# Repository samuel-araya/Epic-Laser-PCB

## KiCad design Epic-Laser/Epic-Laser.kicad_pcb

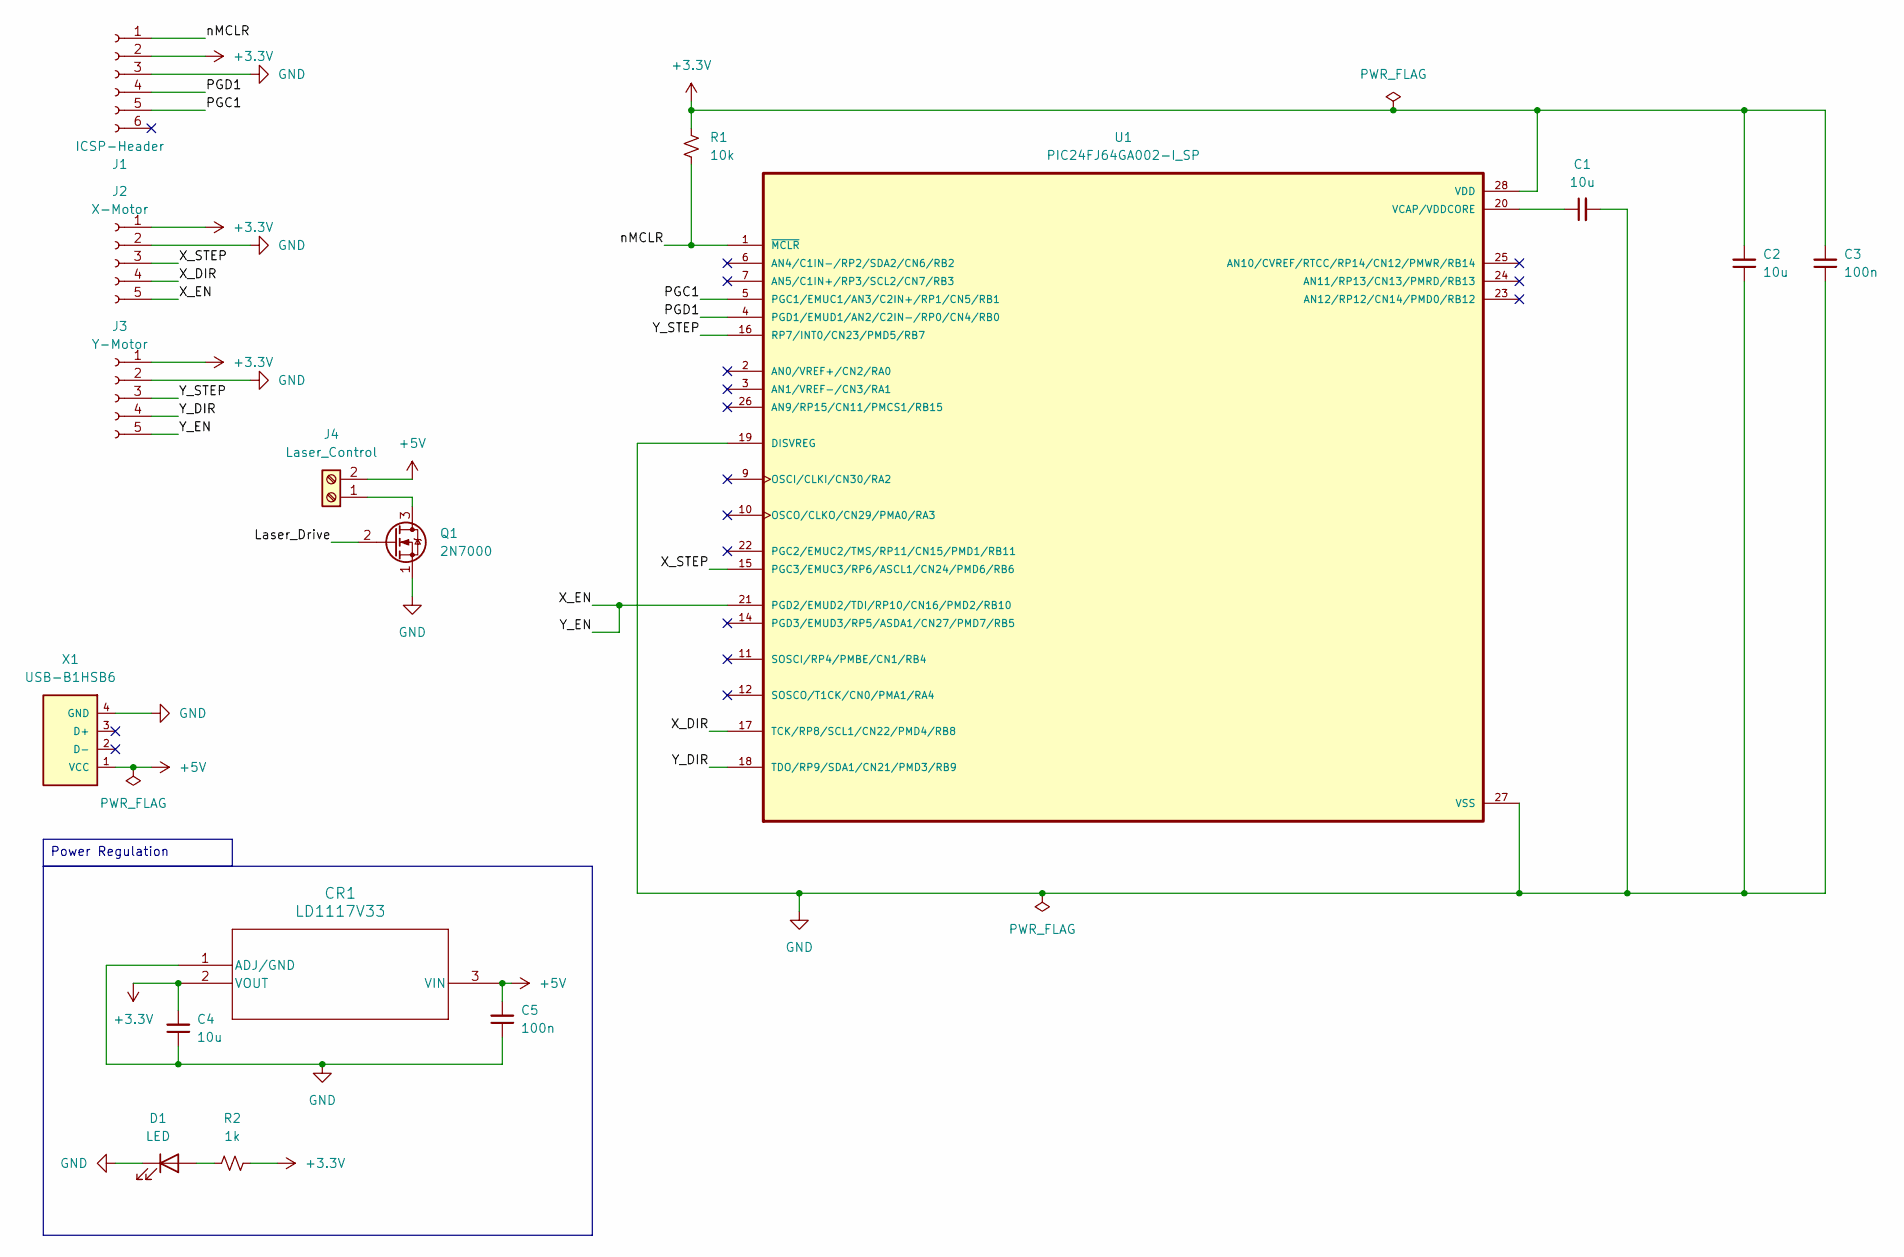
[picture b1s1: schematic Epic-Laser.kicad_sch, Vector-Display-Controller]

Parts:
C1, C2, C4: 10u; C_Disc_D5.0mm_W2.5mm_P2.50mm
C3, C5: 100n; C_Disc_D5.0mm_W2.5mm_P2.50mm
CR1: LD1117V33; TO-220_STM
D1: LED
J1: ICSP-Header; PinSocket_1x07_P2.54mm_Vertical
J2: X-Motor
J3: Y-Motor
J4: Laser_Control
Q1: 2N7000; TO-92_Inline
R1: 10k; R_Axial_DIN0204_L3.6mm_D1.6mm_P5.08mm_Horizontal
R2: 1k
U1: PIC24FJ64GA002-I_SP; DIP787W46P254L3467H508Q28
X1: USB-B1HSB6; OST_USB-B1HSB6

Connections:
+3.3V: C2.2, C3.2, C4.2, CR1.2 (VOUT), J1.2, J2.1, J3.1, R1.1, R2.2, U1.13 (VDD), U1.28 (VDD)
+5V: C5.2, CR1.3 (VIN), J4.2, X1.1 (VCC)
/Laser_Drive: Q1.2 (G), U1.14 (PGD3/EMUD3/RP5/ASDA1/CN27/PMD7/RB5)
/PGC1: J1.5, U1.5 (PGC1/EMUC1/AN3/C2IN+/RP1/CN5/RB1)
/PGD1: J1.4, U1.4 (PGD1/EMUD1/AN2/C2IN-/RP0/CN4/RB0)
/X_DIR: J2.4, U1.17 (TCK/RP8/SCL1/CN22/PMD4/RB8)
/X_EN: J2.5, J3.5, U1.21 (PGD2/EMUD2/TDI/RP10/CN16/PMD2/RB10)
/X_STEP: J2.3, U1.15 (PGC3/EMUC3/RP6/ASCL1/CN24/PMD6/RB6)
/Y_DIR: J3.4, U1.18 (TDO/RP9/SDA1/CN21/PMD3/RB9)
/Y_STEP: J3.3, U1.16 (RP7/INT0/CN23/PMD5/RB7)
/nMCLR: J1.1, R1.2, U1.1 (~MCLR)
GND: C1.2, C2.1, C3.1, C4.1, C5.1, CR1.1 (ADJ/GND), D1.1 (K), J1.3, J2.2, J3.2, Q1.1 (S), U1.8 (VSS), U1.19 (DISVREG), U1.27 (VSS), X1.4 (GND)
unnamed: D1.2 (A), R2.1
unnamed: J4.1, Q1.3 (D)
unnamed: C1.1, U1.20 (VCAP/VDDCORE)

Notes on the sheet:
Power Regulation

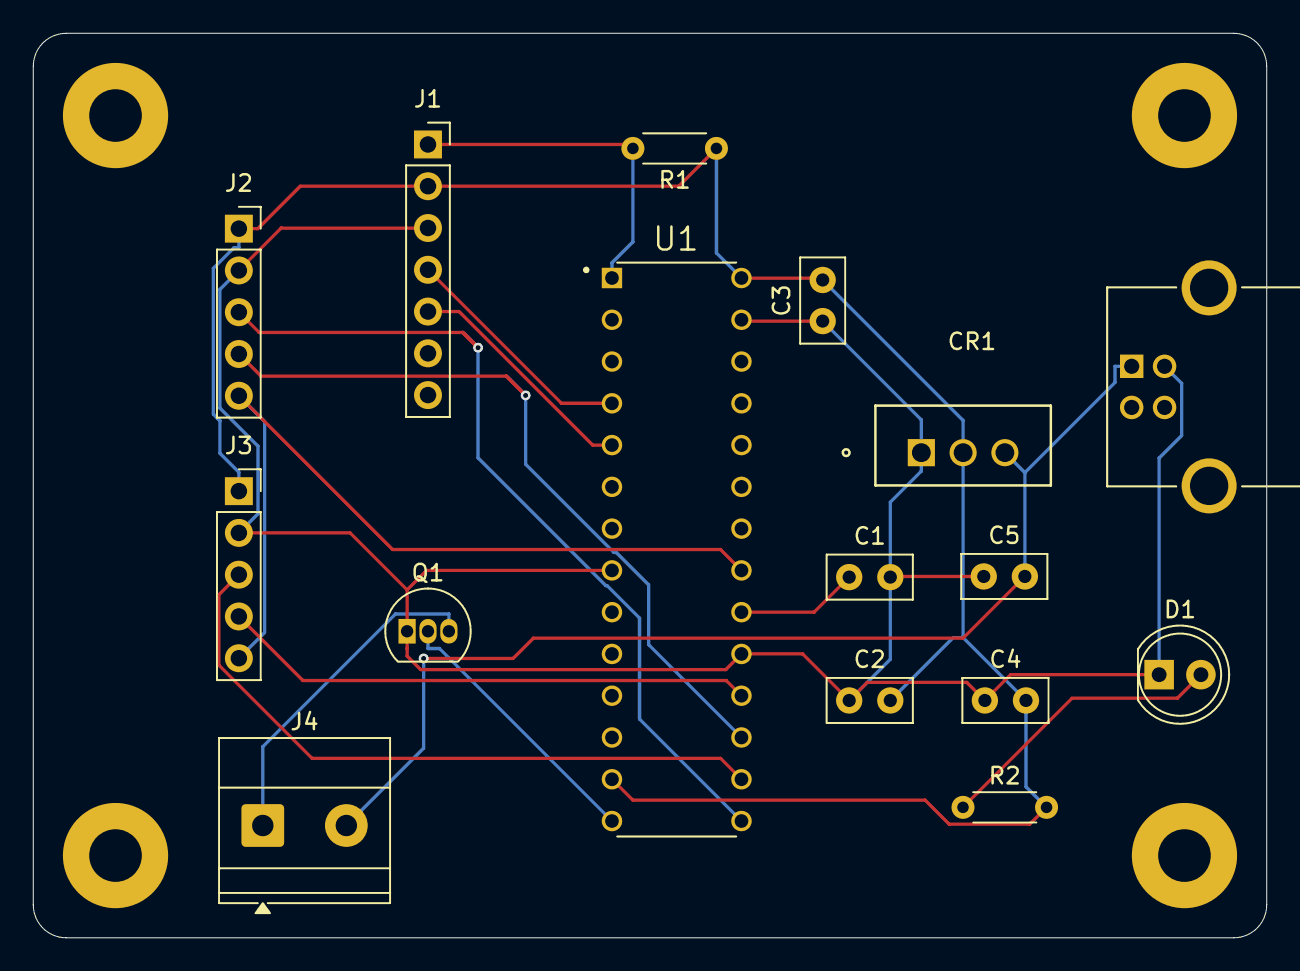
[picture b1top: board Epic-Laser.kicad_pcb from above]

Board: 2 copper layers, 75.0 x 55.0 mm, 20 parts (0 on the bottom side), 15 nets.

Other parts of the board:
REF1, REF2, REF3, REF4: MountingHole_3.2mm_M3_Pad

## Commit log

2026-04-24 init
2026-04-25 Draft-Schematics
2026-04-25 Draft-Board-Layout
